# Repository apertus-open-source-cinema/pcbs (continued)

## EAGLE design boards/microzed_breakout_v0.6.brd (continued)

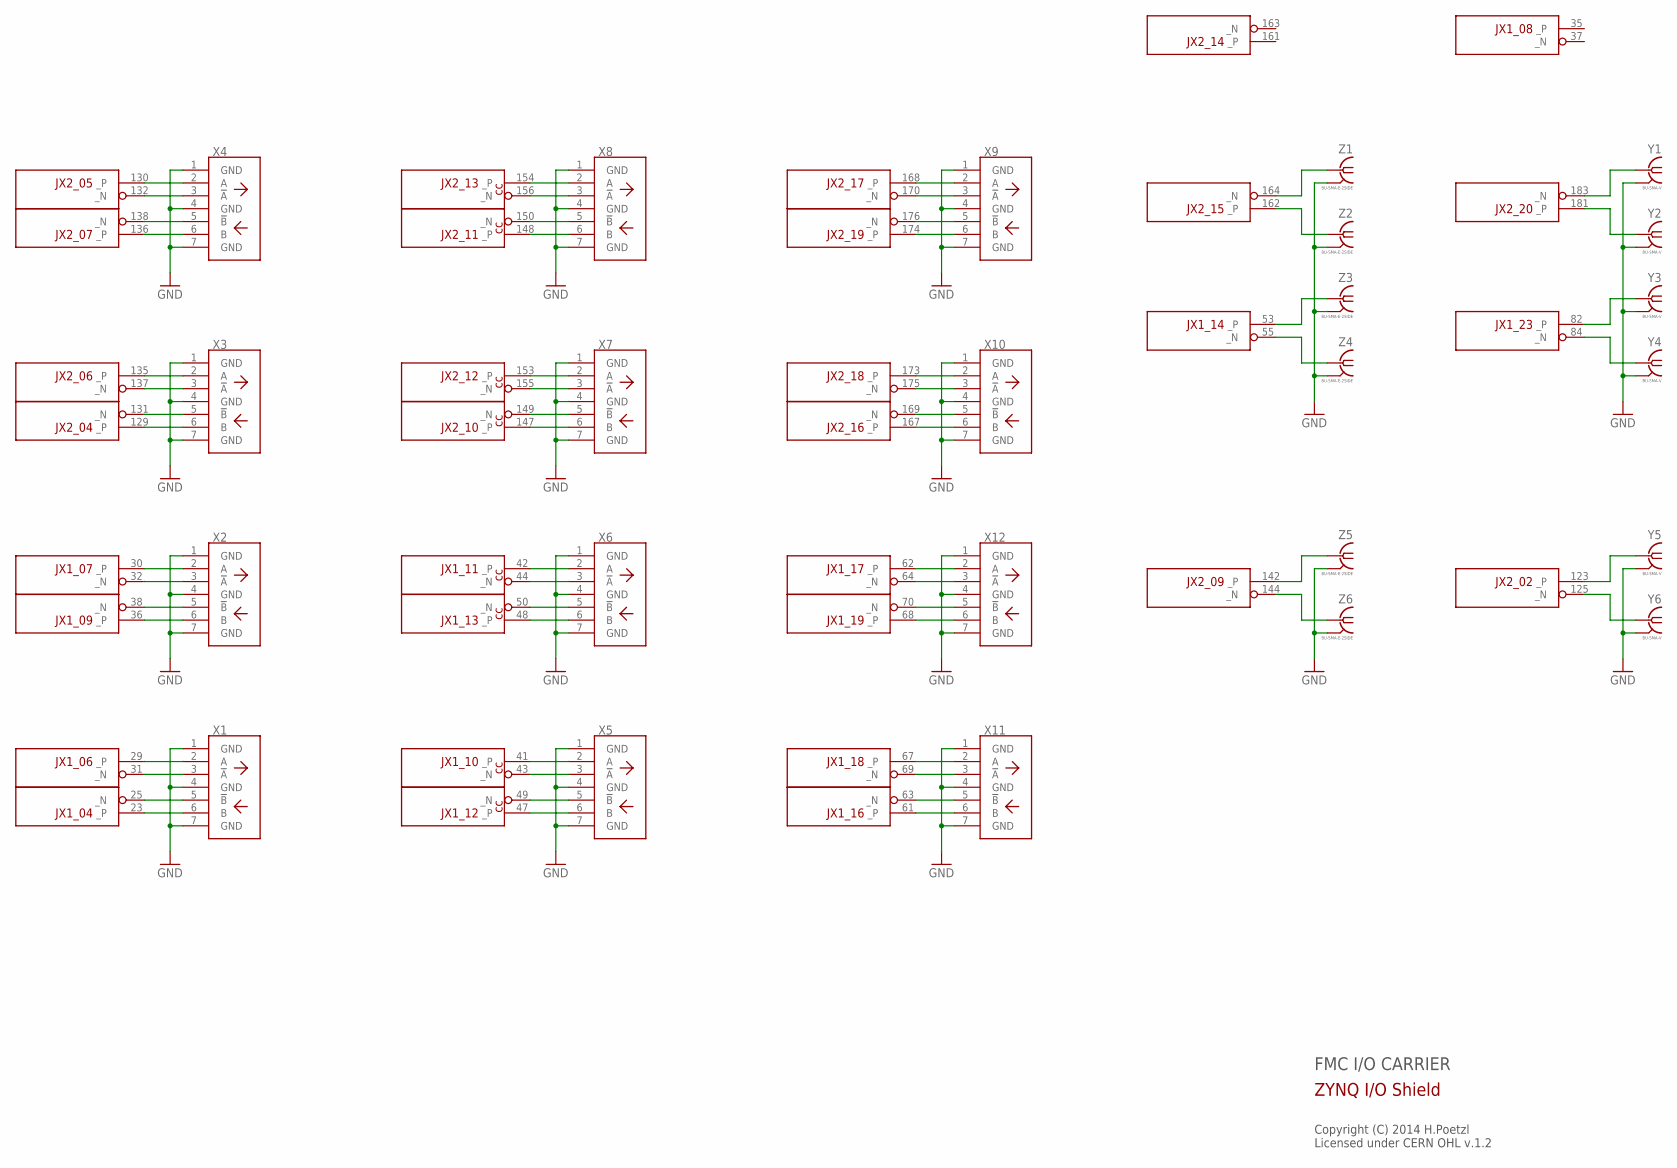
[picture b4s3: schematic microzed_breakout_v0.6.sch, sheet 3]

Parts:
X1, X4, X5, X8, X9, X11: SATA7-SMD-VERT
X2, X3, X6, X7, X10, X12: SATA7-VERT
Y1, Y2, Y3, Y4, Y5, Y6: BU-SMA-V
Z1, Z2, Z3, Z4, Z5, Z6: BU-SMA-E-2SIDE; SMA_EDGE_2SIDE
ZED1: µZ-FCI""; µZ

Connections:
FPGA_VBAT: ZED1.7 (FPGA_VBAT)
GND: X1.1 (GND), X1.4 (GND), X1.7 (GND), X2.1 (GND), X2.4 (GND), X2.7 (GND), X3.1 (GND), X3.4 (GND), X3.7 (GND), X4.1 (GND), X4.4 (GND), X4.7 (GND), X5.1 (GND), X5.4 (GND), X5.7 (GND), X6.1 (GND), X6.4 (GND), X6.7 (GND), X7.1 (GND), X7.4 (GND), X7.7 (GND), X8.1 (GND), X8.4 (GND), X8.7 (GND), X9.1 (GND), X9.4 (GND), X9.7 (GND), X10.1 (GND), X10.4 (GND), X10.7 (GND), X11.1 (GND), X11.4 (GND), X11.7 (GND), X12.1 (GND), X12.4 (GND), X12.7 (GND), Y1.2, Y1.3 (2), Y1.4 (2), Y1.5 (2), Y2.2, Y2.3 (2), Y2.4 (2), Y2.5 (2), Y3.2, Y3.3 (2), Y3.4 (2), Y3.5 (2), Y4.2, Y4.3 (2), Y4.4 (2), Y4.5 (2), Y5.2, Y5.3 (2), Y5.4 (2), Y5.5 (2), Y6.2, Y6.3 (2), Y6.4 (2), Y6.5 (2), Z1.2@1 (2), Z1.2@2 (2), Z1.2@3 (2), Z1.2@4 (2), Z2.2@1 (2), Z2.2@2 (2), Z2.2@3 (2), Z2.2@4 (2), Z3.2@1 (2), Z3.2@2 (2), Z3.2@3 (2), Z3.2@4 (2), Z4.2@1 (2), Z4.2@2 (2), Z4.2@3 (2), Z4.2@4 (2), Z5.2@1 (2), Z5.2@2 (2), Z5.2@3 (2), Z5.2@4 (2), Z6.2@1 (2), Z6.2@2 (2), Z6.2@3 (2), Z6.2@4 (2); also elsewhere on the board
JX1_04_N: X1.5 (!B), ZED1.25 (_N)
JX1_04_P: X1.6 (B), ZED1.23 (_P)
JX1_06_N: X1.3 (!A), ZED1.31 (_N)
JX1_06_P: X1.2 (A), ZED1.29 (_P)
JX1_07_N: X2.3 (!A), ZED1.32 (_N)
JX1_07_P: X2.2 (A), ZED1.30 (_P)
JX1_09_N: X2.5 (!B), ZED1.38 (_N)
JX1_09_P: X2.6 (B), ZED1.36 (_P)
JX1_10_N: X5.3 (!A), ZED1.43 (_N)
JX1_10_P: X5.2 (A), ZED1.41 (_P)
JX1_11_N: X6.3 (!A), ZED1.44 (_N)
JX1_11_P: X6.2 (A), ZED1.42 (_P)
JX1_12_N: X5.5 (!B), ZED1.49 (_N)
JX1_12_P: X5.6 (B), ZED1.47 (_P)
JX1_13_N: X6.5 (!B), ZED1.50 (_N)
JX1_13_P: X6.6 (B), ZED1.48 (_P)
JX1_14_N: Z4.1, ZED1.55 (_N)
JX1_14_P: Z3.1, ZED1.53 (_P)
JX1_16_N: X11.5 (!B), ZED1.63 (_N)
JX1_16_P: X11.6 (B), ZED1.61 (_P)
JX1_17_N: X12.3 (!A), ZED1.64 (_N)
JX1_17_P: X12.2 (A), ZED1.62 (_P)
JX1_18_N: X11.3 (!A), ZED1.69 (_N)
JX1_18_P: X11.2 (A), ZED1.67 (_P)
JX1_19_N: X12.5 (!B), ZED1.70 (_N)
JX1_19_P: X12.6 (B), ZED1.68 (_P)
JX1_23_N: Y4.1, ZED1.84 (_N)
JX1_23_P: Y3.1, ZED1.82 (_P)
JX2_02_N: Y6.1, ZED1.125 (_N)
JX2_02_P: Y5.1, ZED1.123 (_P)
JX2_04_N: X3.5 (!B), ZED1.131 (_N)
JX2_04_P: X3.6 (B), ZED1.129 (_P)
JX2_05_N: X4.3 (!A), ZED1.132 (_N)
JX2_05_P: X4.2 (A), ZED1.130 (_P)
JX2_06_N: X3.3 (!A), ZED1.137 (_N)
JX2_06_P: X3.2 (A), ZED1.135 (_P)
JX2_07_N: X4.5 (!B), ZED1.138 (_N)
JX2_07_P: X4.6 (B), ZED1.136 (_P)
JX2_09_N: Z6.1, ZED1.144 (_N)
JX2_09_P: Z5.1, ZED1.142 (_P)
JX2_10_N: X7.5 (!B), ZED1.149 (_N)
JX2_10_P: X7.6 (B), ZED1.147 (_P)
JX2_11_N: X8.5 (!B), ZED1.150 (_N)
JX2_11_P: X8.6 (B), ZED1.148 (_P)
JX2_12_N: X7.3 (!A), ZED1.155 (_N)
JX2_12_P: X7.2 (A), ZED1.153 (_P)
JX2_13_N: X8.3 (!A), ZED1.156 (_N)
JX2_13_P: X8.2 (A), ZED1.154 (_P)
JX2_15_N: Z1.1, ZED1.164 (_N)
JX2_15_P: Z2.1, ZED1.162 (_P)
JX2_16_N: X10.5 (!B), ZED1.169 (_N)
JX2_16_P: X10.6 (B), ZED1.167 (_P)
JX2_17_N: X9.3 (!A), ZED1.170 (_N)
JX2_17_P: X9.2 (A), ZED1.168 (_P)
JX2_18_N: X10.3 (!A), ZED1.175 (_N)
JX2_18_P: X10.2 (A), ZED1.173 (_P)
JX2_19_N: X9.5 (!B), ZED1.176 (_N)
JX2_19_P: X9.6 (B), ZED1.174 (_P)
JX2_20_N: Y1.1, ZED1.183 (_N)
JX2_20_P: Y2.1, ZED1.181 (_P)

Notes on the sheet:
FMC I/O CARRIER
Copyright (C) 2014 H.Poetzl Licensed under CERN OHL v.1.2
ZYNQ I/O Shield

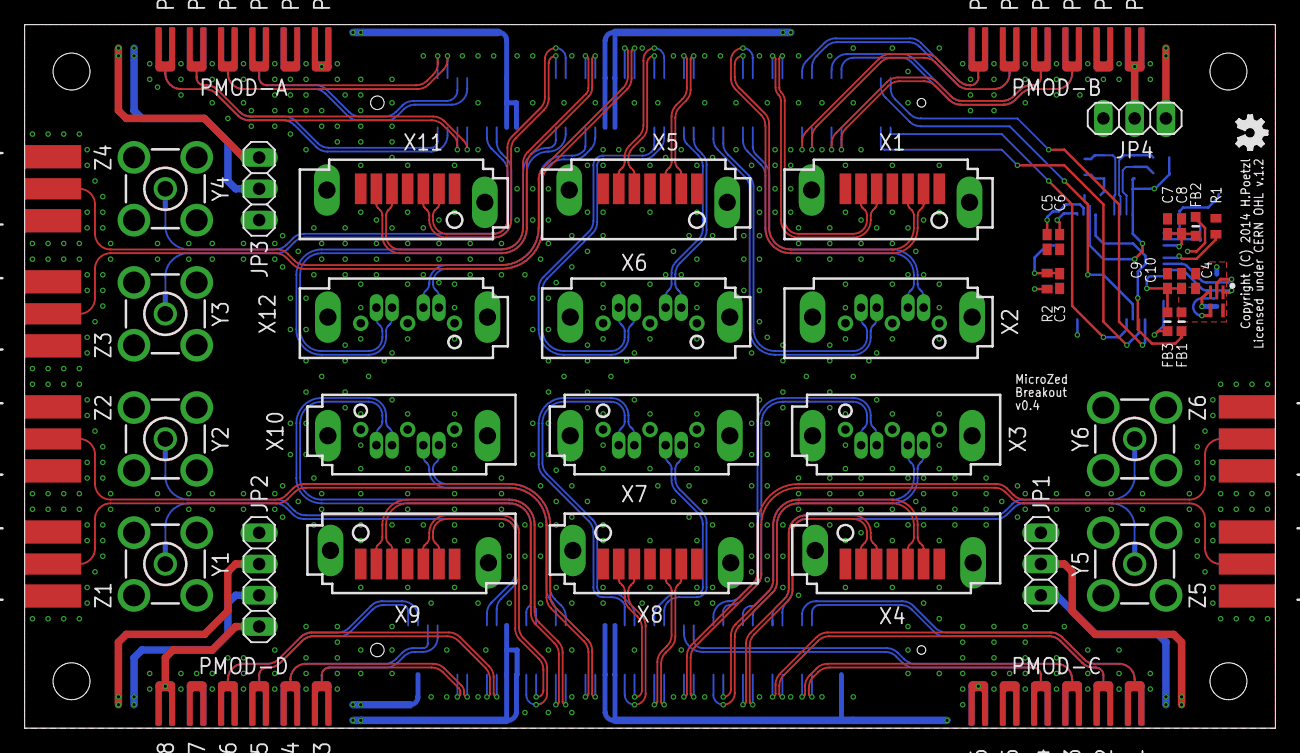
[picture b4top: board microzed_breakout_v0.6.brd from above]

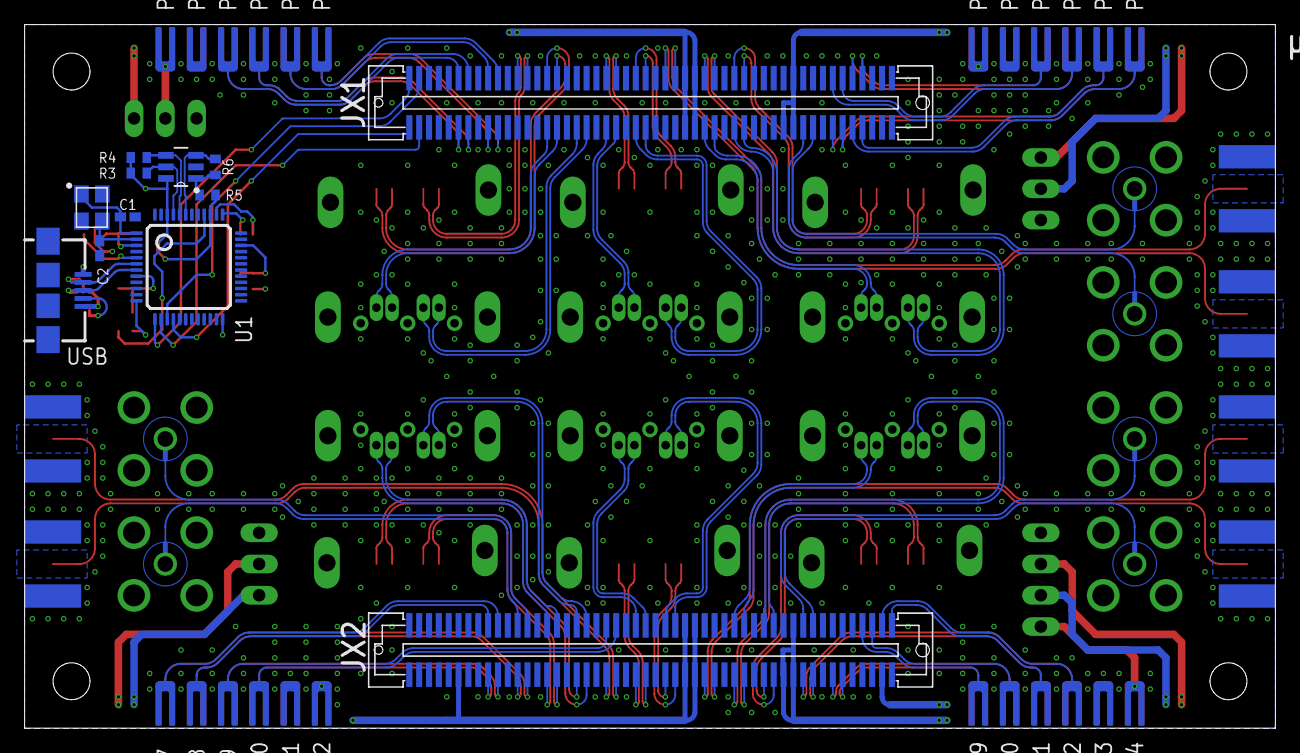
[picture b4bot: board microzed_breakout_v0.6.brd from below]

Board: 4 copper layers, 101.6 x 57.1 mm, 102 parts (35 on the bottom side), 123 nets.

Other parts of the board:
LOGO1: OSHW_LOGO_FILLX0100-NT; OSHW_FILLX100_NOTEXT

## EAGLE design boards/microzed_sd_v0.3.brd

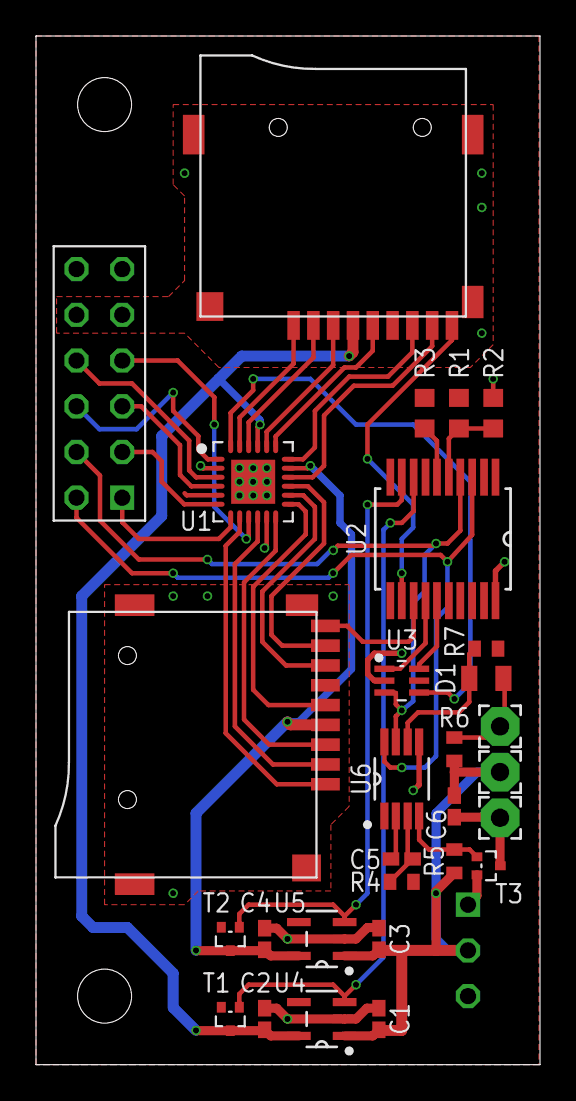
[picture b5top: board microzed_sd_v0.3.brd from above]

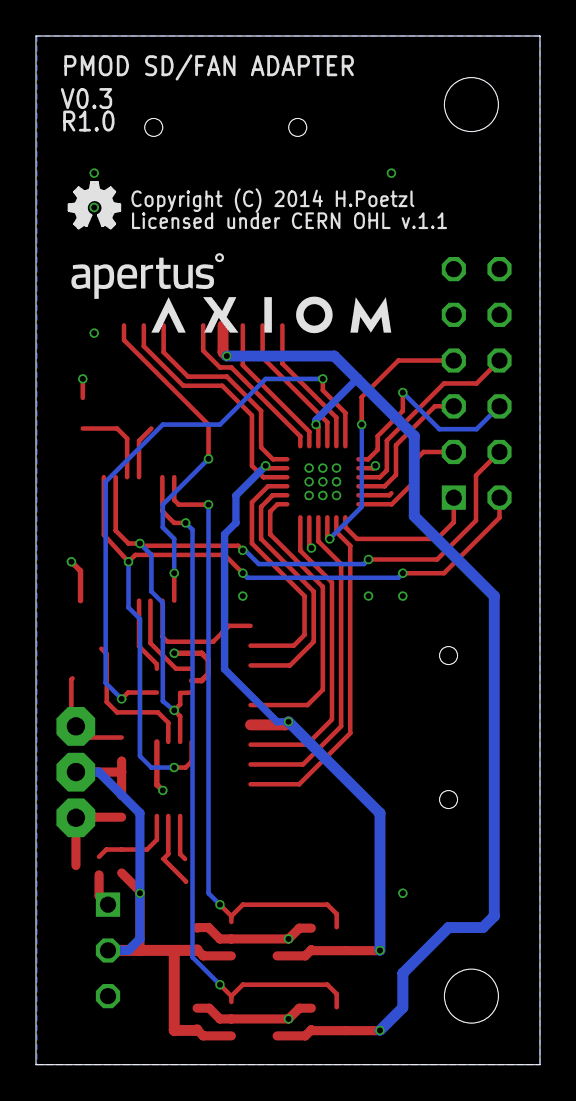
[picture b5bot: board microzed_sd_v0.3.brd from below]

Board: 4 copper layers, 28.0 x 57.1 mm, 32 parts (3 on the bottom side), 40 nets.

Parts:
C1, C2, C3, C4, C6: 1µ; C0402K
C5: 2n2; C0402K
D1: MICROMELF-W
LOGO1: OSHW_LOGO_FILLX0100-NT; OSHW_FILLX100_NOTEXT
PAD1, PAD2, PAD3: WIREPAD2,15/1,0; 2,15/1,0
R1, R2: R0603
R3: 10k; R0603
R4: 100R; R0402
R5: 2k2; R0402
R6, R7: 10k; R0402
T1, T2: PMR670UPE; SOT416
T3: PMR290UNE; SOT416
U0: µZ-PMOD-NOHOLES; µZ-TOP-NOHOLES
U1: TXS02612; S-PWQFN-N24
U2: MCP23009-E/SS; SOP65P780X200-20N
U3: 74LVC1G98DW-7; SOT65P210X110-6N
U4, U5: LD6836TD/30P; SOT95P275X110-5N
U6: EMC2101-ACZL; SOP65P490X110-8N
U$1: APERTUS_LOGO334X100; APERTUS_LOGO_334X100
U$13: AXIOM_LOGO525X80; AXIOM_LOGO_525X80
µSD0, µSD1: MICRO-SD3; TF-MICRO-SD_PP3

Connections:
A_CLK: U0.J5-4, U1.9
A_CMD: U0.J5-3, U1.4
A_DAT0: U0.J5-2, U1.6
A_DAT1: U0.J5-1, U1.7
A_DAT2: U0.J5-9, U1.1
A_DAT3: U0.J5-10, U1.3
B0_CLK: U1.19, µSD0.5
B0_CMD: U1.20, µSD0.3
B0_DAT0: U1.18, µSD0.7
B0_DAT1: U1.16, µSD0.8
B0_DAT2: U1.23, µSD0.1
B0_DAT3: U1.22, µSD0.2
B1_CLK: U1.13, µSD1.5
B1_CMD: U1.12, µSD1.3
B1_DAT0: U1.14, µSD1.7
B1_DAT1: U1.15, µSD1.8
B1_DAT2: U1.8, µSD1.1
B1_DAT3: U1.10, µSD1.2
CD0: U2.12, µSD0.CD
CD1: U2.13, µSD1.CD
FAN: C6.2, PAD1.1, T3.3
GND: C1.2, C2.2, C3.2, C4.2, R2.1, T3.2, U0.J5-5, U0.J5-11, U0.JP4-1, U0.JP4-3, U1.2, U1.11, U1.EPAD, U2.20, U3.2, U4.2, U5.2, U6.5, µSD0.6, µSD0.MT1, µSD0.MT2, µSD0.MT3, µSD0.MT4, µSD1.6, µSD1.MT1, µSD1.MT2, µSD1.MT3, µSD1.MT4
unnamed: U2.14, U3.1
unnamed: U2.15, U3.6
unnamed: R1.1, R2.2, U2.5
unnamed: R3.1, U2.6
unnamed: C5.2, U6.2
unnamed: C5.1, R4.1, U6.3
unnamed: R5.2, T3.1, U6.4
unnamed: D1.A, R7.2, U6.6
PWR0: T1.1, U2.8, U4.3
PWR1: T2.1, U2.9, U5.3
SCL: U0.J5-7, U2.3, U6.8
SDA: U0.J5-8, U2.4, U3.3, U6.7
SEL: U1.24, U3.4
TACH: D1.C, PAD3.1, R6.2
VCC: R1.2, R3.2, R7.1, T1.2, T2.2, U0.J5-6, U0.J5-12, U1.5, U2.1, U3.5, U6.1
VCC0: C2.1, T1.3, U1.21, U4.5, µSD0.4
VCC1: C4.1, T2.3, U1.17, U5.5, µSD1.4
VDD: C1.1, C3.1, C6.1, PAD2.1, R5.1, R6.1, U0.JP4-2, U4.1, U5.1

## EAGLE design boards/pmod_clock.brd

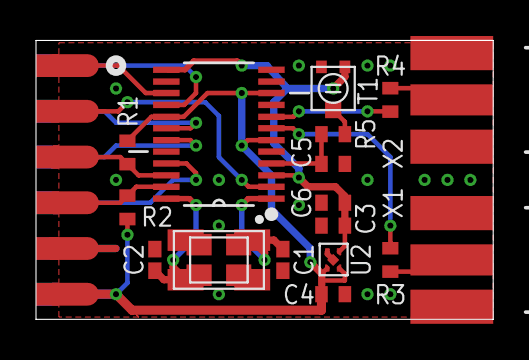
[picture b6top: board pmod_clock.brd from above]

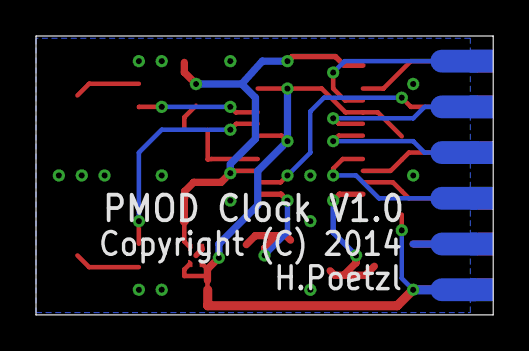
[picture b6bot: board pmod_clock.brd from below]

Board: 2 copper layers, 25.4 x 15.5 mm, 29 parts (6 on the bottom side), 19 nets.

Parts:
C1, C2: 10p; C0402K
C3, C4: 1µ; C0402
C5: 0.1µ; C0402
C6: 100n; C0402
PAD1, PAD2, PAD3, PAD4, PAD5, PAD6, PAD7, PAD8, PAD9, PAD10, PAD11, PAD12: SMD1.27-3.175HR
Q1: SMD-4P-2G5.0X3.2+3.2X2.5; MIX
R1, R2: 4k7; R0402
R3, R4: 22R; R0402
R5: 100k; R0402
T1: PVZ2A; TRIM-PVZ2A
U1: CDCE949PW; SOP65P640X120-24N
U2: LD6805K18H; NXP_LD6805
X1, X2: BU-SMA-E; SMA-EDGE

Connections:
+1V8: C3.1, C6.1, T1.1, U1.3, U1.13, U2.1
+3V3: C4.1, PAD6.1, PAD12.1, R1.2, R2.2, U1.6, U1.10, U1.17, U2.3, U2.4
GND: C1.2, C2.2, C3.2, C4.2, C5.2, C6.2, PAD5.1, PAD11.1, Q1.2, Q1.2@, Q1.4, Q1.4@, T1.3, U1.5, U1.9, U1.14, U1.20, U2.2, U2.5, X1.2@3, X1.2@4, X2.2@3, X2.2@4
unnamed: C1.1, Q1.1, Q1.1@, U1.1
unnamed: C2.1, Q1.3, Q1.3@, U1.24
unnamed: R4.1, X2.1
unnamed: R3.1, X1.1
unnamed: R5.1, T1.2
unnamed: R3.2, U1.7
S0: PAD2.1, U1.2
S1: PAD4.1, R2.1, U1.23
S2: PAD3.1, R1.1, U1.22
VCNTR: C5.1, R5.2, U1.4
Y1: PAD10.1, U1.21
Y2: PAD9.1, U1.19
Y3: PAD8.1, U1.18
Y5: R4.2, U1.8
Y6: PAD7.1, U1.16
Y7: PAD1.1, U1.15
